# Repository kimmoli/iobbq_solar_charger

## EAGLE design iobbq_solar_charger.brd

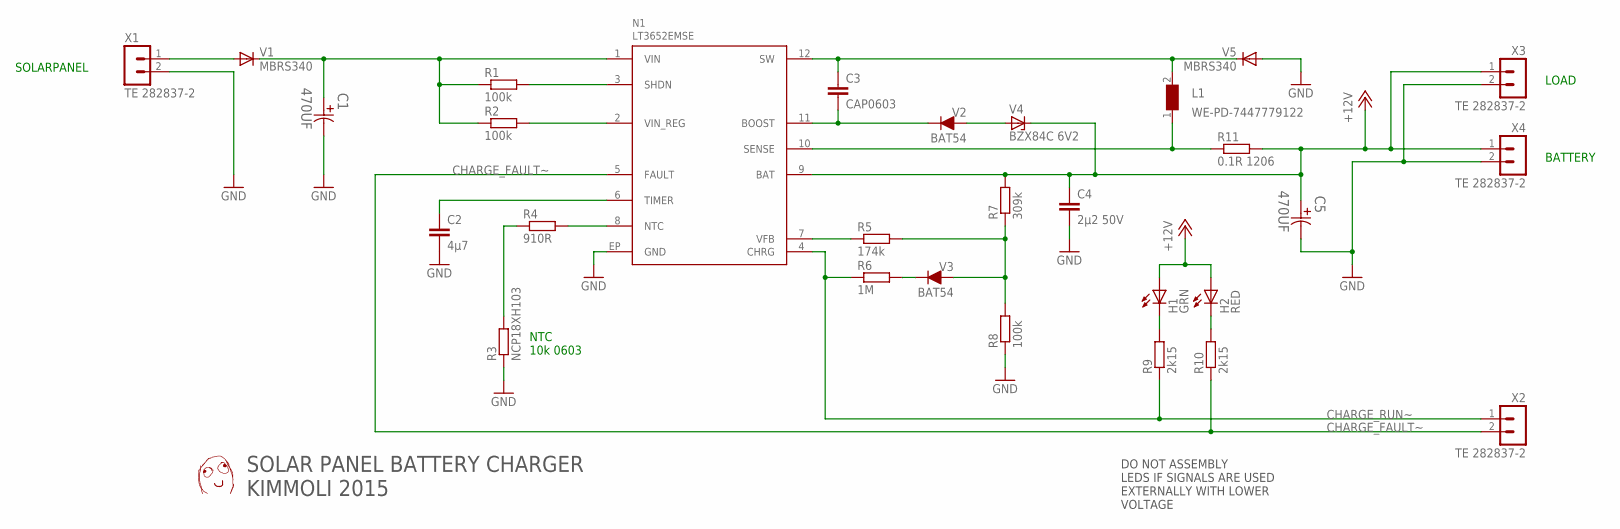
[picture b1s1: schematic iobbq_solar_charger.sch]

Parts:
C1, C5: 470UF; CAPAE1350X1400N
C2: 4µ7; C0805
C3: CAP0603; C0603
C4: 2µ2 50V; C0805
H1: GRN; LED3MM
H2: RED; LED3MM
L1: WE-PD-7447779122; WE-PD_7332/7345_PLASTIC_BASE
N1: LT3652EMSE; MSOP-12-EP-065
R1, R2, R8: 100k; R0603
R3: NCP18XH103; R0603
R4: 910R; R0603
R5: 174k; R0603
R6: 1M; R0603
R7: 309k; R0603
R9, R10: 2k15; R1206
R11: 0.1R 1206; R1206
U$2: DAFUG
V1, V5: MBRS340; SMC
V2, V3: BAT54; SOT23
V4: BZX84C 6V2; TO236
X1, X2, X3, X4: TE 282837-2; TE_RUUVILIITIN2

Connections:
+12V: C4.1, C5.1, H1.A, H2.A, N1.9 (BAT), R7.2, R11.2, V4.C, X3.1, X4.1
CHARGE_FAULT~: N1.5 (FAULT), R10.1, X2.2
CHARGE_RUN~: N1.4 (CHRG), R6.1, R9.1, X2.1
GND: C1.2, C2.2, C4.2, C5.2, N1.EP (GND), R3.1, R8.1, V5.A, X1.2, X3.2, X4.2
unnamed: H2.K (C), R10.2
unnamed: H1.K (C), R9.2
unnamed: V1.A, X1.1
unnamed: C1.1, N1.1 (VIN), R1.1, R2.1, V1.C
unnamed: N1.3 (SHDN), R1.2
unnamed: N1.2 (VIN_REG), R2.2
unnamed: C2.1, N1.6 (TIMER)
unnamed: C3.2, N1.11 (BOOST), V2.3
unnamed: C3.1, L1.2, N1.12 (SW), V5.C
unnamed: V2.1, V4.A
unnamed: L1.1, N1.10 (SENSE), R11.1
unnamed: R3.2, R4.1
unnamed: N1.8 (NTC), R4.2
unnamed: R5.2, R7.1, R8.2, V3.1
unnamed: R6.2, V3.3
unnamed: N1.7 (VFB), R5.1

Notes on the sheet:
NTC 10k 0603
SOLARPANEL
BATTERY
LOAD
DO NOT ASSEMBLY LEDS IF SIGNALS ARE USED EXTERNALLY WITH LOWER VOLTAGE
SOLAR PANEL BATTERY CHARGER KIMMOLI 2015

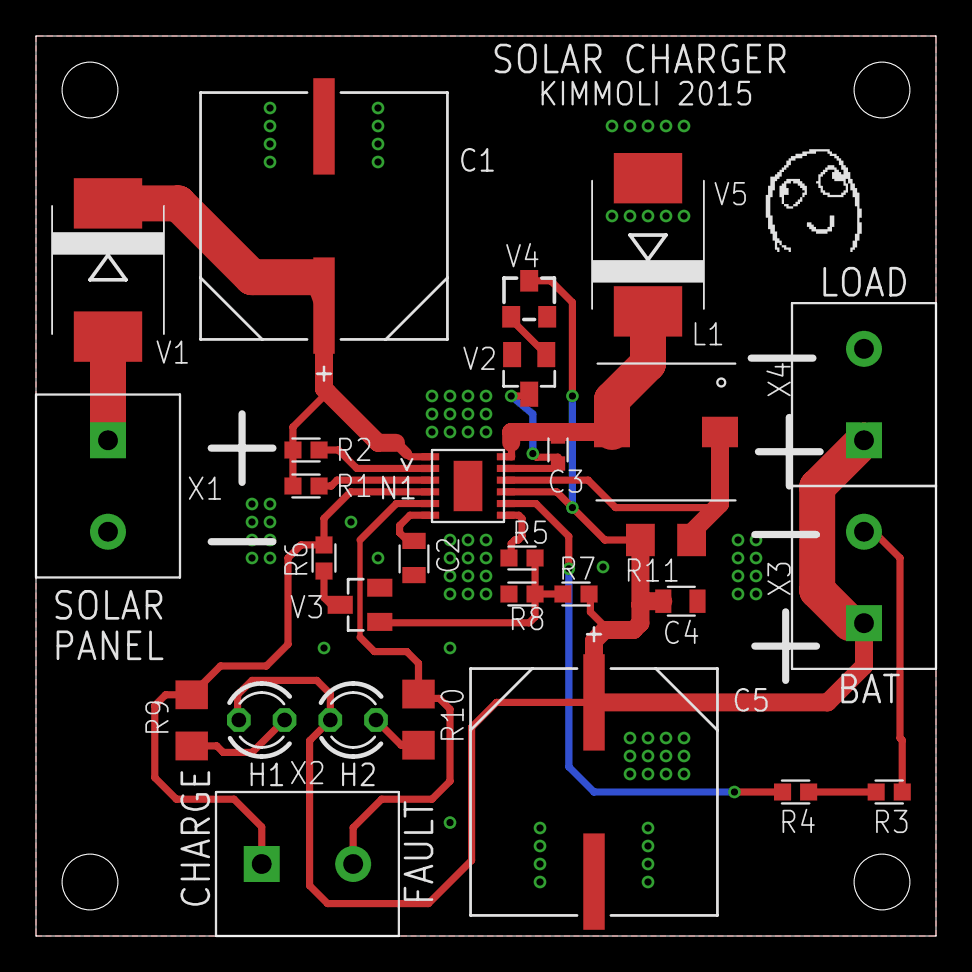
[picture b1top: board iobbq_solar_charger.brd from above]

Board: 2 copper layers, 50.0 x 50.0 mm, 30 parts (0 on the bottom side), 20 nets.

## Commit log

2015-04-03 initial version
2015-04-05 update values
